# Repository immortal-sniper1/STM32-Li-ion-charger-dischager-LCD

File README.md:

# STM32-Li-ion-charger-dischager-LCD

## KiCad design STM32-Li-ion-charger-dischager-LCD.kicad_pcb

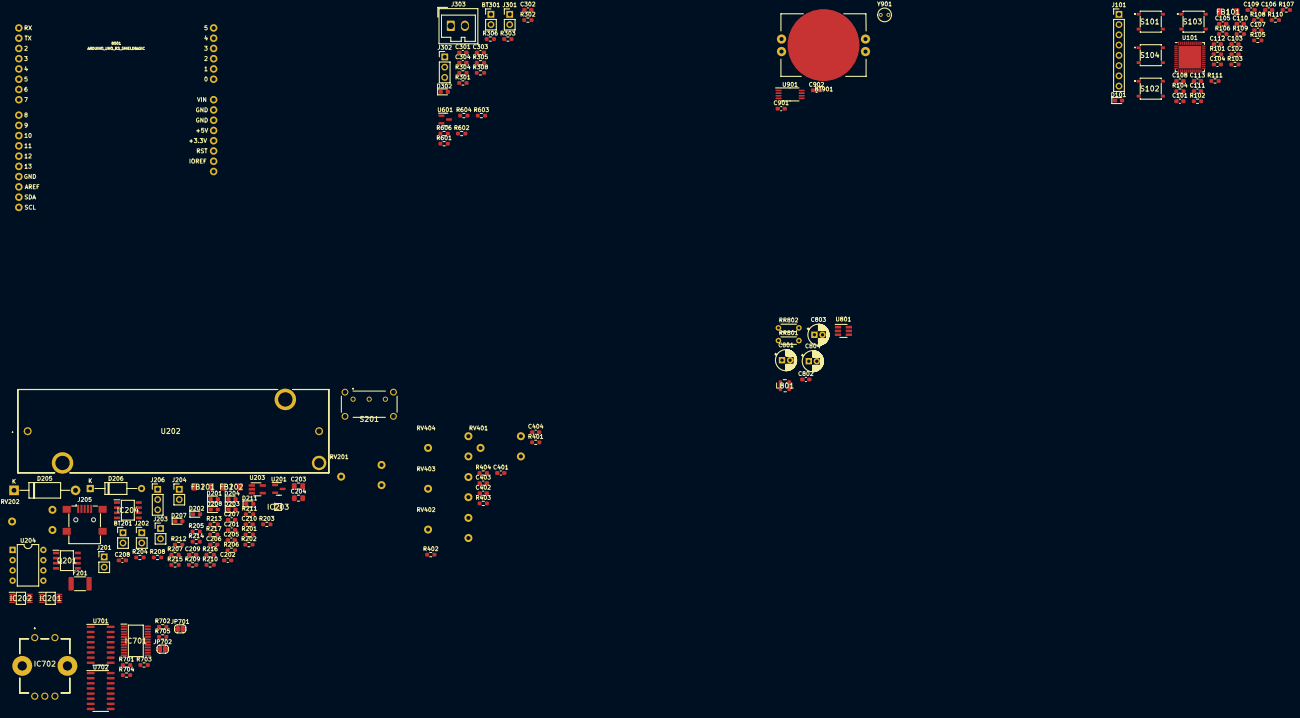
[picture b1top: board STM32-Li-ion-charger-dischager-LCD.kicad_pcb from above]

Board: 2 copper layers, 149 parts (0 on the bottom side), 95 nets, no tracks yet.

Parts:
B501: ARDUINO_UNO_R3_SHIELDBASIC; UNO_R3_SHIELD
BT201, BT301: Battery_Cell; PinHeader_1x02_P2.54mm_Vertical
BT901: Battery_Cell; BATHLD001THM
C101, C102, C104, C105: 24P; C_0603_1608Metric_Pad1.08x0.95mm_HandSolder
C103: 4u7; C_0603_1608Metric_Pad1.08x0.95mm_HandSolder
C106, C107, C108, C109, C111, C112, C113, C207, C208, C303, C304: 100n; C_0603_1608Metric_Pad1.08x0.95mm_HandSolder
C110: C_Small; C_0603_1608Metric_Pad1.08x0.95mm_HandSolder
C201, C202, C209, C210: 4.7u; C_0603_1608Metric_Pad1.08x0.95mm_HandSolder
C203, C204: 1u; C_0805_2012Metric_Pad1.18x1.45mm_HandSolder
C205: 10n; C_0603_1608Metric_Pad1.08x0.95mm_HandSolder
C206, C301, C302, C401, C402, C403, C404: 1u; C_0603_1608Metric_Pad1.08x0.95mm_HandSolder
C801, C803, C804: 22u; CP_Radial_D5.0mm_P2.00mm
C802: 22p optional; C_0603_1608Metric_Pad1.08x0.95mm_HandSolder
C901, C902: 15pF; C_0603_1608Metric_Pad1.08x0.95mm_HandSolder
D101, D201, D202, D203, D204, D302: LED_Small; LED_0603_1608Metric_Pad1.05x0.95mm_HandSolder
D205: D_Shockley; D_DO-15_P15.24mm_Horizontal
D206: D_Shockley; D_A-405_P12.70mm_Horizontal
D207, D208, D211: LED_Small Green; LED_0603_1608Metric_Pad1.05x0.95mm_HandSolder
F201: Polyfuse_Small; Fuse_1812_4532Metric_Pad1.30x3.40mm_HandSolder
FB101, FB201, FB202: HI1806T600R-10; BEADC4516X185N
IC201, IC202: MCP73834T-FCI_UN; SOP50P490X110-10N
IC203: ISL9120IIAZ-TR5696; BGA9C40P3X3_141X141X55
IC204: AP2112M-3.3TRG1; SOIC127P600X170-8N
IC701: XRA1203IG24TR-F; SOP65P640X120-24N
IC702: PEC12R-4230F-S0024; PEC12R4230FS0024
J101: Conn_01x08; PinHeader_1x08_P2.54mm_Vertical
J201: Conn_01x02_Male; PinHeader_1x02_P2.54mm_Vertical
J202, J203, J204, J301: Conn_01x02; PinHeader_1x02_P2.54mm_Vertical
J205: USB_B_Mini; USB_Mini-B_Lumberg_2486_01_Horizontal
J206, J302: Conn_01x03; PinHeader_1x03_P2.54mm_Vertical
J303: Conn_01x02; Wago_734-132_1x02_P3.50mm_Vertical
JP701, JP702: J1; SolderJumper-2_P1.3mm_Open_RoundedPad1.0x1.5mm
L801: NRH3012T2R2MN 2,2uH; NRH3012T220MNV
Q201: DMG9933USD-13; SOIC127P600X175-8N
R101, R102, R103, R104, R105, R107, R108, R109, R110, R111, R205, R206, R207, R208, R214, R215, R302, R303, R306, R601, R602, R701, R702, R703, R704, R705: 10k; R_0603_1608Metric_Pad0.98x0.95mm_HandSolder
R106, R305, R308, R606: 1k; R_0603_1608Metric_Pad0.98x0.95mm_HandSolder
R201, R202, R203, R204: 470; R_0603_1608Metric_Pad0.98x0.95mm_HandSolder
R209, R210, R211, R212, R401, R402, R403, R404, R603, R604: 50k; R_0603_1608Metric_Pad0.98x0.95mm_HandSolder
R213: 10k+ pullup; R_0603_1608Metric_Pad0.98x0.95mm_HandSolder
R216, R217: 330; R_0603_1608Metric_Pad0.98x0.95mm_HandSolder
R301: 47k; R_0603_1608Metric_Pad0.98x0.95mm_HandSolder
R304: 5k; R_0603_1608Metric_Pad0.98x0.95mm_HandSolder
RR801, RR802: R_Small; R_Axial_DIN0204_L3.6mm_D1.6mm_P5.08mm_Horizontal
RV201, RV202: 10k; 2002102255
RV401, RV402, RV403, RV404: 47k; 2002102255
S101, S102, S103, S104: PTS526_SK15_SMTR2_LFS; PTS526SK15SMTR2LFS
S201: EG1224 SPDT switch; EG1224
U101: STM32L151C6Ux; QFN-48-1EP_7x7mm_P0.5mm_EP5.6x5.6mm
U201: APX810S05; SOT-23
U202: 1043
U203: D1213A-02SM; SOT-23-5_HandSoldering
U204: NE555P; DIP-8_W7.62mm
U601: LM4040DBZ-3; SOT-23
U701, U702: MC74VHC4052DR2G; SOIC-16_3.9x9.9mm_P1.27mm
U801: DIO6012BCST6; SOT-23-6_Handsoldering
U901: MCP79412; TSSOP-8_4.4x3mm_P0.65mm
Y901: 32.7680kHz; Crystal_C38-LF_D3.0mm_L8.0mm_Vertical

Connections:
3v3_enable: IC204.5 (EN), R213.1, U801.1 (EN)
+3.3VA: C205.1, C206.1, FB201.2, R606.1, U101.9 (VDDA)
+3V3: B501.3.3V, C103.1, C106.1, C108.1, C109.1, FB201.1, IC701.24 (VCC), J101.8, R101.1, R103.2, R104.2, R105.2, R107.2, R108.2, R109.2, R110.2, R111.2, R216.2, R602.2, R703.2, R704.2, R705.2, RV401.3, RV402.3, RV403.3, RV404.3, S201.2 (COM), U101.24 (VDD), U101.36 (VDD), U101.48 (VDD), U701.16 (VCC), U702.16 (VCC), U901.8 (VCC)
+5V: C110.1, D101.2 (A), D201.2 (A), D202.2 (A), D203.2 (A), D204.2 (A), FB101.2, IC201.1 (VDD_1), IC201.2 (VDD_2), IC202.1 (VDD_1), IC202.2 (VDD_2)
+12V: R603.2, U204.4 (R), U204.8 (VCC)
+BATT: C201.1, IC201.9 (VBAT_1), IC201.10 (VBAT_2), J201.1, J206.1, J302.3, Q201.1 (S1), R209.1, U201.3 (Vcc), U202.1 (+)
+VDC: C203.1, C801.1, D205.1 (K), D206.1 (K), IC204.8 (VIN), J206.3, Q201.3 (S2), R213.2, U801.4 (IN)
/BOOT0: R102.2, U101.44 (BOOT0)
/BattDischarger/Measured_BATT+: BT301.1 (+), C303.2, C304.1, J303.2, R306.1
/NRST: J101.2, R101.2, S101.3 (NO_1), S101.4 (NO_2), U101.7 (NRST)
/PowerManagement/Drains: Q201.5 (D2_1), Q201.6 (D2_2), Q201.7 (D1_1), Q201.8 (D1_2)
/PowerManagement/VBUS_RAW: F201.1, J205.1 (VBUS)
/PowerManagement/VBUS_RAW2: F201.2, FB202.1
/PowerManagement/buck/inductor_buck: L801.1, U801.3 (LX)
/PowerManagement/buck_out: C802.1, C803.1, C804.1, L801.2, RR801.1, S201.1 (PIN1)
/PowerManagement/lin_reg: C204.1, IC204.1 (VOUT), S201.3 (PIN2)
/RTC/Li-ion-20mm-cell: BT901.1 (+), U901.3 (BATT)
/RTC/X1: C901.2, U901.1 (X1), Y901.1
/RTC/X2: C902.2, U901.2 (X2), Y901.2
/multiplexing+gpio_extenders/A0: IC701.21 (A0), JP701.2 (B), R703.1
/multiplexing+gpio_extenders/A1: IC701.2 (A1), JP702.2 (B), R704.1
/multiplexing+gpio_extenders/RESET: IC701.3 (RESET#), R705.1
/multiplexing+gpio_extenders/enable1: IC701.15 (P10), R701.1, U701.6 (ENABLE)
/multiplexing+gpio_extenders/enable2: IC701.16 (P11), R702.1, U702.6 (ENABLE)
/osc_in: C104.2, U101.5 (PH0)
/osc_out: C105.2, U101.6 (PH1)
ADC1: U101.10 (PA0), U701.13 (X_OUT)
ADC2: U101.11 (PA1), U701.3 (Y_OUT)
ADC3: U101.12 (PA2), U702.13 (X_OUT)
ADC4: U101.13 (PA3), U702.3 (Y_OUT)
BATT2+: BT201.1 (+), C202.1, IC202.9 (VBAT_1), IC202.10 (VBAT_2), J302.1, R210.1
D+: J205.3 (D+), U203.4 (CH2)
D-: J205.2 (D-), U203.3 (CH1)
GND: B501.GND@ (GND), BT201.2 (-), BT301.2 (-), BT901.2 (-), C101.1, C102.1, C103.2, C104.1, C105.1, C106.2, C107.1, C108.2, C109.2, C110.2, C111.1, C112.1, C113.1, C201.2, C202.2, C203.2, C204.2, C205.2, C206.2, C207.1, C208.1, C210.2, C301.2, C302.1, C801.2, C803.2, C804.2, C901.1, C902.1, D207.1 (K), D208.1 (K), D211.1 (K), IC201.5 (VSS), IC202.5 (VSS), IC204.6 (GND_1), IC204.7 (GND_2), IC701.12 (GND), J101.1, J101.7, J201.2, J202.1, J203.2, J204.2, J205.5 (GND), J205.6 (Shield), J301.1, J302.2, J303.1, JP701.1 (A), JP702.1 (A), R106.2, R205.1, R206.1, R207.1, R208.1, R211.2, R212.2, R301.2, R304.2, R305.2, R601.1, R604.1, R701.2, R702.2, RR802.2, RV201.2, RV202.2, RV401.1, RV402.1, RV403.1, RV404.1, S201.MH1, S201.MH2, S201.MH3, S201.MH4, U101.8 (VSSA), U101.23 (VSS), U101.35 (VSS), U101.47 (VSS), U101.49 (VSS), U201.2 (GND), U202.2 (-), U203.2 (VSS), U204.1 (GND), U601.2 (A), U701.7 (VEE), U701.8 (GND), U702.7 (VEE), U702.8 (GND), U801.2 (GND), U901.4 (VSS)
I2C_CLK: IC701.22 (SCL), R111.1, U101.42 (PB6), U901.6 (SCL)
I2C_SDA: IC701.23 (SDA), R110.1, U101.43 (PB7), U901.5 (SDA)
LCD_CS: B501.A3, IC701.11 (P7)
LCD_RST: B501.A4, IC701.4 (P0)
unnamed: C101.2, U101.3 (PC14)
unnamed: C102.2, U101.4 (PC15)
unnamed: C107.2, S101.1 (COM_1), S101.2 (COM_2)
unnamed: C111.2, S102.1 (COM_1), S102.2 (COM_2)
unnamed: C112.2, S103.1 (COM_1), S103.2 (COM_2)
unnamed: C113.2, S104.1 (COM_1), S104.2 (COM_2)
unnamed: C207.2, U204.5 (CV)
unnamed: C208.2, U204.2 (TR), U204.6 (THR)
unnamed: C209.1, U204.3 (Q)
unnamed: C301.1, R302.1
unnamed: C302.2, R303.1
unnamed: C304.2, R308.1
unnamed: C401.2, R401.2, RV401.2
unnamed: C402.2, R402.2, RV402.2
unnamed: C403.2, R403.2, RV403.2
unnamed: C404.2, R404.2, RV404.2
unnamed: C802.2, RR801.2, RR802.1, U801.6 (FB)
unnamed: D101.1 (K), R106.1
unnamed: D201.1 (K), R201.1
unnamed: D202.1 (K), R202.1
unnamed: D203.1 (K), R203.1
unnamed: D204.1 (K), R204.1
unnamed: D206.2 (A), J202.2
unnamed: D207.2 (A), R214.1, R215.2
unnamed: D208.2 (A), R216.1
unnamed: D211.2 (A), R217.1
unnamed: IC201.3 (STAT1), R201.2
unnamed: IC201.4 (STAT2), R202.2
unnamed: IC201.6 (PROG), RV201.1
unnamed: IC201.8 (THERM), R207.2
unnamed: IC202.3 (STAT1), R203.2
unnamed: IC202.4 (STAT2), R204.2
unnamed: IC202.6 (PROG), RV202.1
unnamed: IC202.8 (THERM), R208.2
unnamed: J203.1, RV201.3
unnamed: J204.1, RV202.3
unnamed: J206.2, R217.2
unnamed: Q201.2 (G1), R205.2, U201.1 (RESET)
unnamed: R301.1, R302.2
PB0: R103.1, S102.3 (NO_1), S102.4 (NO_2)
PB1: R105.1, S104.3 (NO_1), S104.4 (NO_2)
PB9: R104.1, S103.3 (NO_1), S103.4 (NO_2)
SPI_CLK: B501.D13, R109.1, U101.26 (PB13)
SPI_MISO: B501.D12, R108.1, U101.27 (PB14)
SPI_MOSI: B501.D11 (*D11), R107.1, U101.28 (PB15)
TOUCH_X: B501.A2, U101.16 (PA6)
TOUCH_Y: B501.A1, U101.17 (PA7)
UART_RX: J101.4, U101.30 (PA9)
UART_TX: J101.3, U101.31 (PA10)
VBUS: D205.2 (A), FB101.1, FB202.2, Q201.4 (G2), R206.2, R214.2, R215.1, U203.5 (VCC)
V_ref: R606.2, U601.1 (K)
bat1_v: R209.2, R211.1, U701.12 (X0)
bat2_v: R210.2, R212.1, U701.1 (Y0)
measured_batt_v: R304.1, R306.2, U702.12 (X0)
mux1: IC701.13 (P8), U701.9 (B), U702.9 (B)
mux2: IC701.14 (P9), U701.10 (A), U702.10 (A)
thermistor: R601.2, U702.2 (Y2)

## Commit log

2022-03-21 soft
2022-04-06 more work
